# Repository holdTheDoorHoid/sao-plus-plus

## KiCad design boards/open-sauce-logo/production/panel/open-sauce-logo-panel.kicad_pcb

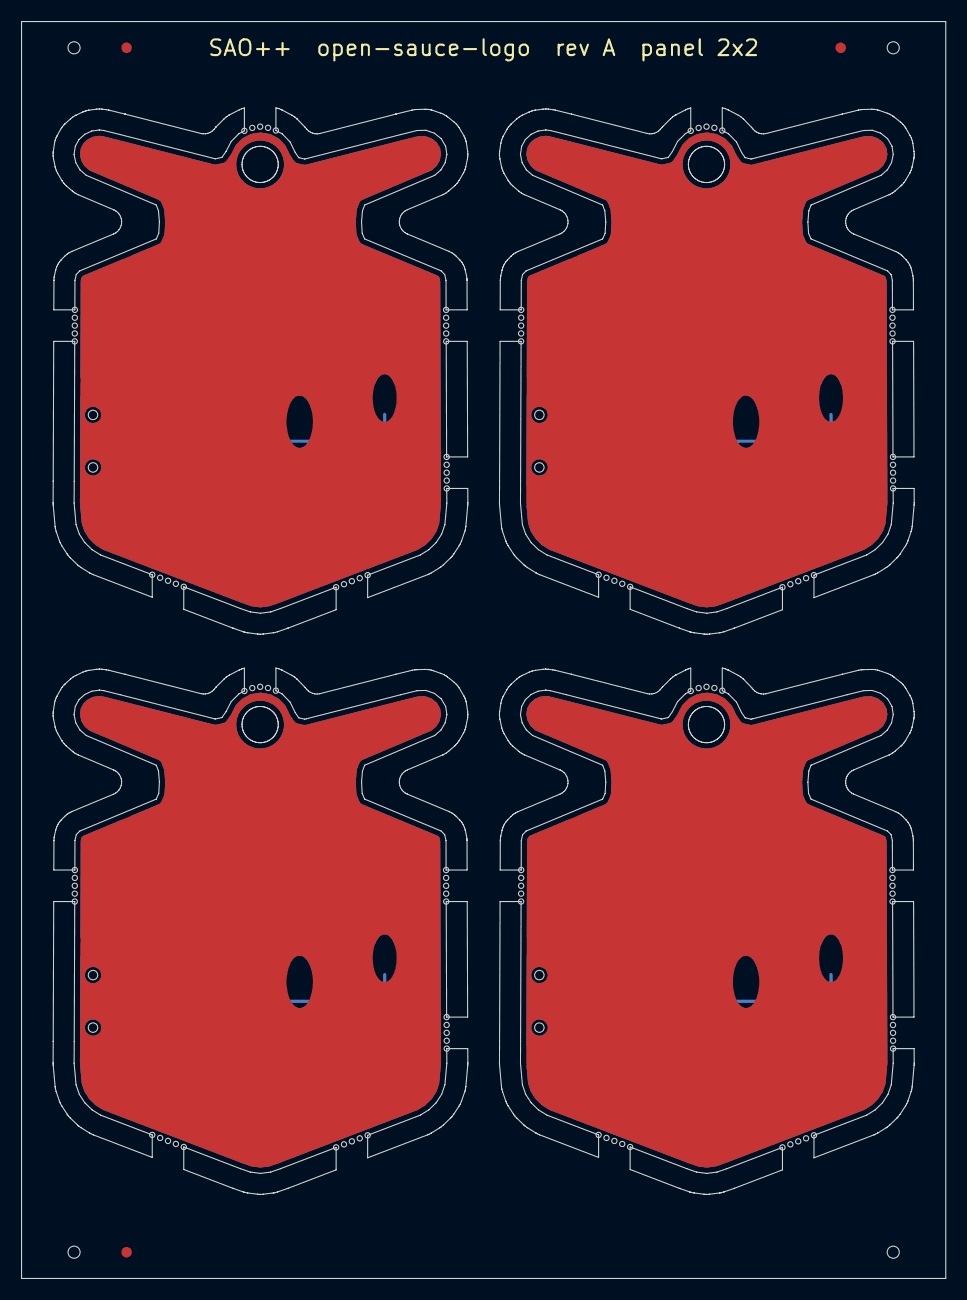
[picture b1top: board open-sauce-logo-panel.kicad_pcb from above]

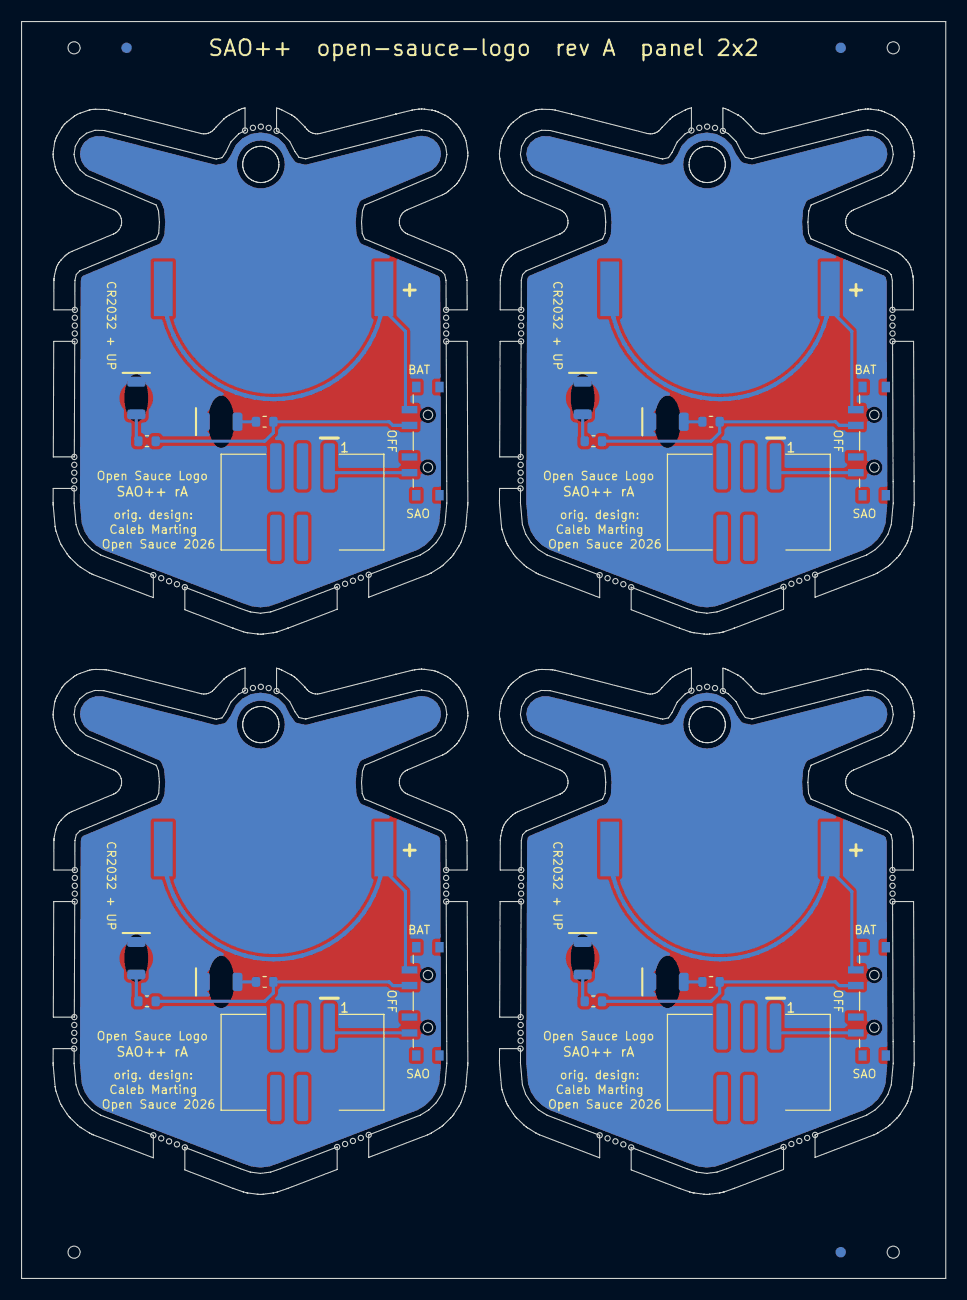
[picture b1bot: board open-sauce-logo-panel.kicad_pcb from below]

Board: 2 copper layers, 88.0 x 119.6 mm, 28 parts (28 on the bottom side), 24 nets.

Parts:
BT101, BT201, BT301, BT401: CR2032; SAOPP_BAT-01_CR2032_SMD_TE_BAT-HLD-001
D101, D102, D201, D202, D301, D302, D401, D402: red; SAOPP_LED-10_1206_ReverseMount_ThroughBoard
J101, J201, J301, J401: SAO v1.69bis; SAOPP_CONN-01_BoxHeader_2x03_P2.54mm_SMD_XFCN_BH254VS-6P
R101, R102, R201, R202, R301, R302, R401, R402: 1.3k; SAOPP_R_0603_1608Metric
SW101, SW201, SW301, SW401: SAO / OFF / BAT; SAOPP_SW-01_Slide_SP3T_CK_PCM13SMTR

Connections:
B2-GND: BT201.2, D201.1, D202.1, J201.2
B2-LED1_A: D201.2, R201.2
B2-LED2_A: D202.2, R202.2
B2-VBAT: BT201.1, SW201.4
B2-VLOAD: R201.1, R202.1, SW201.3
B2-VSAO: J201.1, SW201.1
B3-GND: BT301.2, D301.1, D302.1, J301.2
B3-LED1_A: D301.2, R301.2
B3-LED2_A: D302.2, R302.2
B3-VBAT: BT301.1, SW301.4
B3-VLOAD: R301.1, R302.1, SW301.3
B3-VSAO: J301.1, SW301.1
B4-GND: BT401.2, D401.1, D402.1, J401.2
B4-LED1_A: D401.2, R401.2
B4-LED2_A: D402.2, R402.2
B4-VBAT: BT401.1, SW401.4
B4-VLOAD: R401.1, R402.1, SW401.3
B4-VSAO: J401.1, SW401.1
GND: BT101.2, D101.1, D102.1, J101.2
LED1_A: D101.2, R101.2
LED2_A: D102.2, R102.2
VBAT: BT101.1, SW101.4
VLOAD: R101.1, R102.1, SW101.3
VSAO: J101.1, SW101.1

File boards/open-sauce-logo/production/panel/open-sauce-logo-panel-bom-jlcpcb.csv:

Comment,Designator,Footprint,LCSC Part #
CR2032,"BT101,BT201,BT301,BT401",SAOPP_BAT-01_CR2032_SMD_TE_BAT-HLD-001,C7501066
red,"D101,D102,D201,D202,D301,D302,D401,D402",SAOPP_LED-10_1206_ReverseMount_ThroughBoard,C125107
SAO v1.69bis,"J101,J201,J301,J401",SAOPP_CONN-01_BoxHeader_2x03_P2.54mm_SMD_XFCN_BH254VS-6P,C492445
1.3k,"R101,R102,R201,R202,R301,R302,R401,R402",SAOPP_R_0603_1608Metric,C22767
SAO / OFF / BAT,"SW101,SW201,SW301,SW401",SAOPP_SW-01_Slide_SP3T_CK_PCM13SMTR,C221842

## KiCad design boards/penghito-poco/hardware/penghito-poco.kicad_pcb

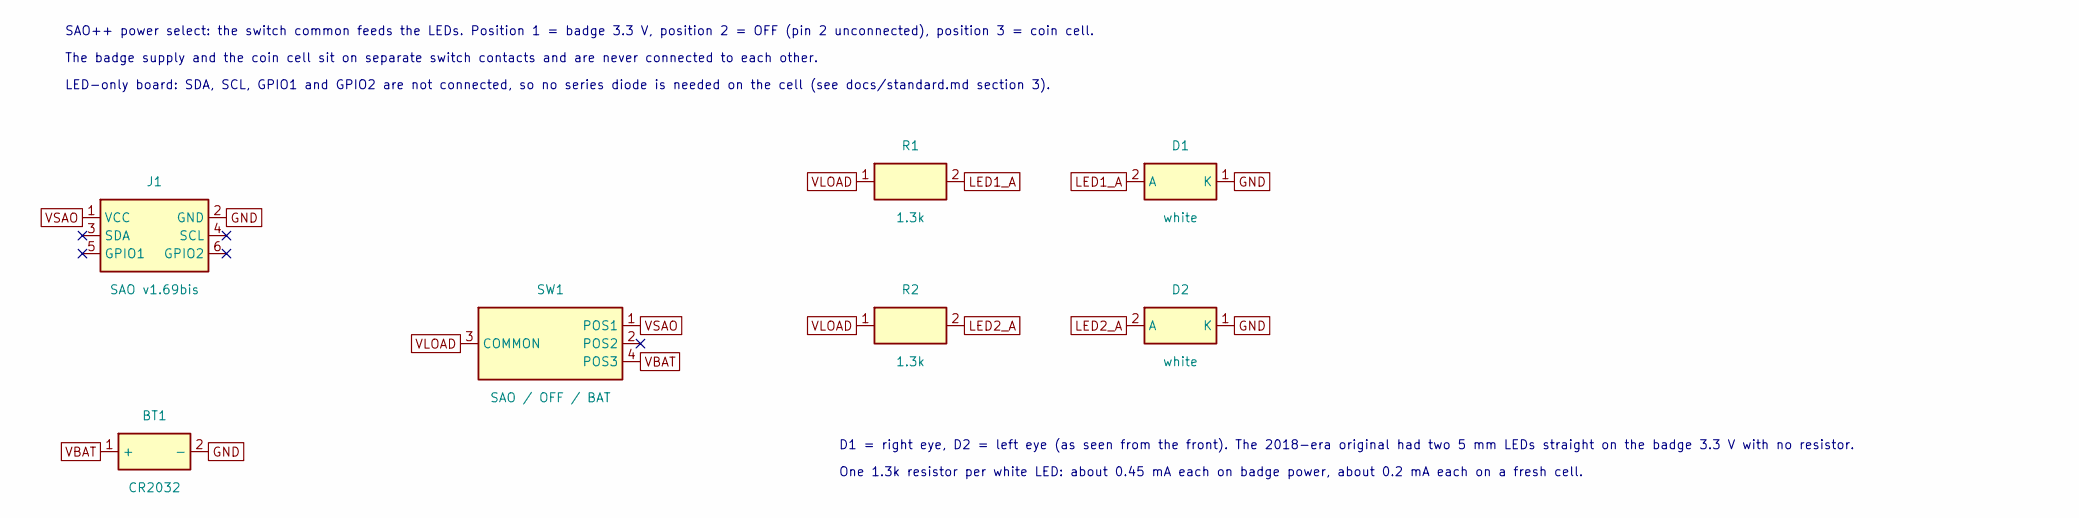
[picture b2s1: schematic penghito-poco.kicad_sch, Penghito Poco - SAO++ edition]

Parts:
BT1: CR2032; SAOPP_BAT-01_CR2032_SMD_TE_BAT-HLD-001; MPN BAT-HLD-001; LCSC C7501066
D1, D2: white; SAOPP_LED-10_1206_ReverseMount_ThroughBoard; MPN LTW-C230DS; LCSC C575513
J1: SAO v1.69bis; SAOPP_CONN-01_BoxHeader_2x03_P2.54mm_SMD_XFCN_BH254VS-6P; MPN BH254VS-6P; LCSC C492445
R1, R2: 1.3k; SAOPP_R_0603_1608Metric; MPN 0603WAF1301T5E; LCSC C22767
SW1: SAO / OFF / BAT; SAOPP_SW-01_Slide_SP3T_CK_PCM13SMTR; MPN PCM13SMTR; LCSC C221842

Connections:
GND: BT1.2 (-), D1.1 (K), D2.1 (K), J1.2 (GND)
LED1_A: D1.2 (A), R1.2
LED2_A: D2.2 (A), R2.2
VBAT: BT1.1 (+), SW1.4 (POS3)
VLOAD: R1.1, R2.1, SW1.3 (COMMON)
VSAO: J1.1 (VCC), SW1.1 (POS1)

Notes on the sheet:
SAO++ power select: the switch common feeds the LEDs. Position 1 = badge 3.3 V, position 2 = OFF (pin 2 unconnected), position 3 = coin cell.
The badge supply and the coin cell sit on separate switch contacts and are never connected to each other.
LED-only board: SDA, SCL, GPIO1 and GPIO2 are not connected, so no series diode is needed on the cell (see docs/standard.md section 3).
D1 = right eye, D2 = left eye (as seen from the front). The 2018-era original had two 5 mm LEDs straight on the badge 3.3 V with no resistor.
One 1.3k resistor per white LED: about 0.45 mA each on badge power, about 0.2 mA each on a fresh cell.

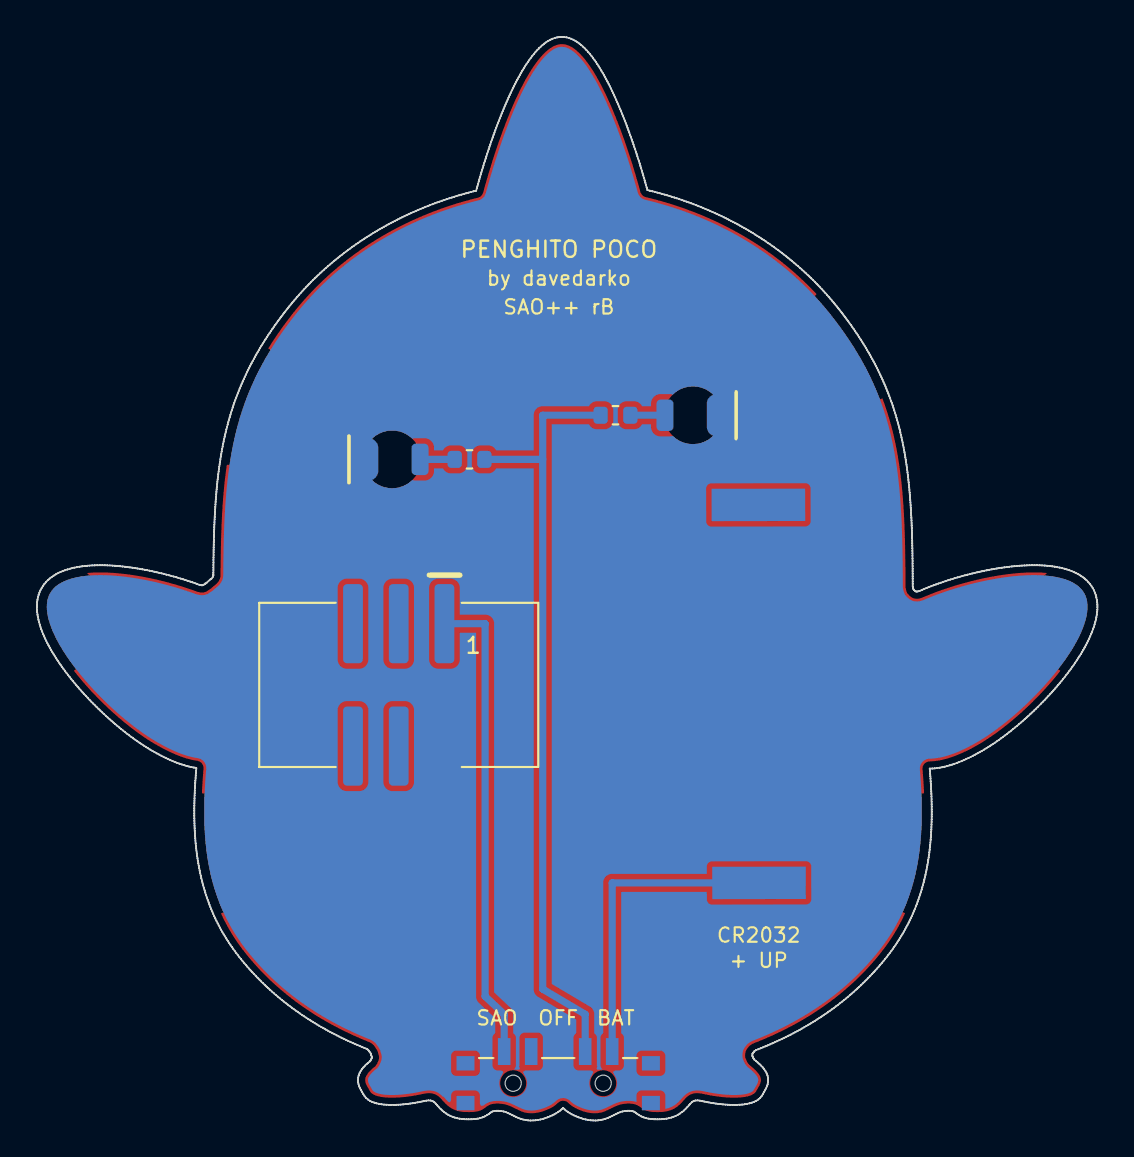
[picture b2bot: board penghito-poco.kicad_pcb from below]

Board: 2 copper layers, 58.9 x 60.2 mm, 7 parts (7 on the bottom side), 6 nets.

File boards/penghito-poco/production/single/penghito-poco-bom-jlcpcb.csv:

Comment,Designator,Footprint,LCSC Part #
CR2032,BT1,SAOPP_BAT-01_CR2032_SMD_TE_BAT-HLD-001,C7501066
white,"D1,D2",SAOPP_LED-10_1206_ReverseMount_ThroughBoard,C575513
SAO v1.69bis,J1,SAOPP_CONN-01_BoxHeader_2x03_P2.54mm_SMD_XFCN_BH254VS-6P,C492445
1.3k,"R1,R2",SAOPP_R_0603_1608Metric,C22767
SAO / OFF / BAT,SW1,SAOPP_SW-01_Slide_SP3T_CK_PCM13SMTR,C221842

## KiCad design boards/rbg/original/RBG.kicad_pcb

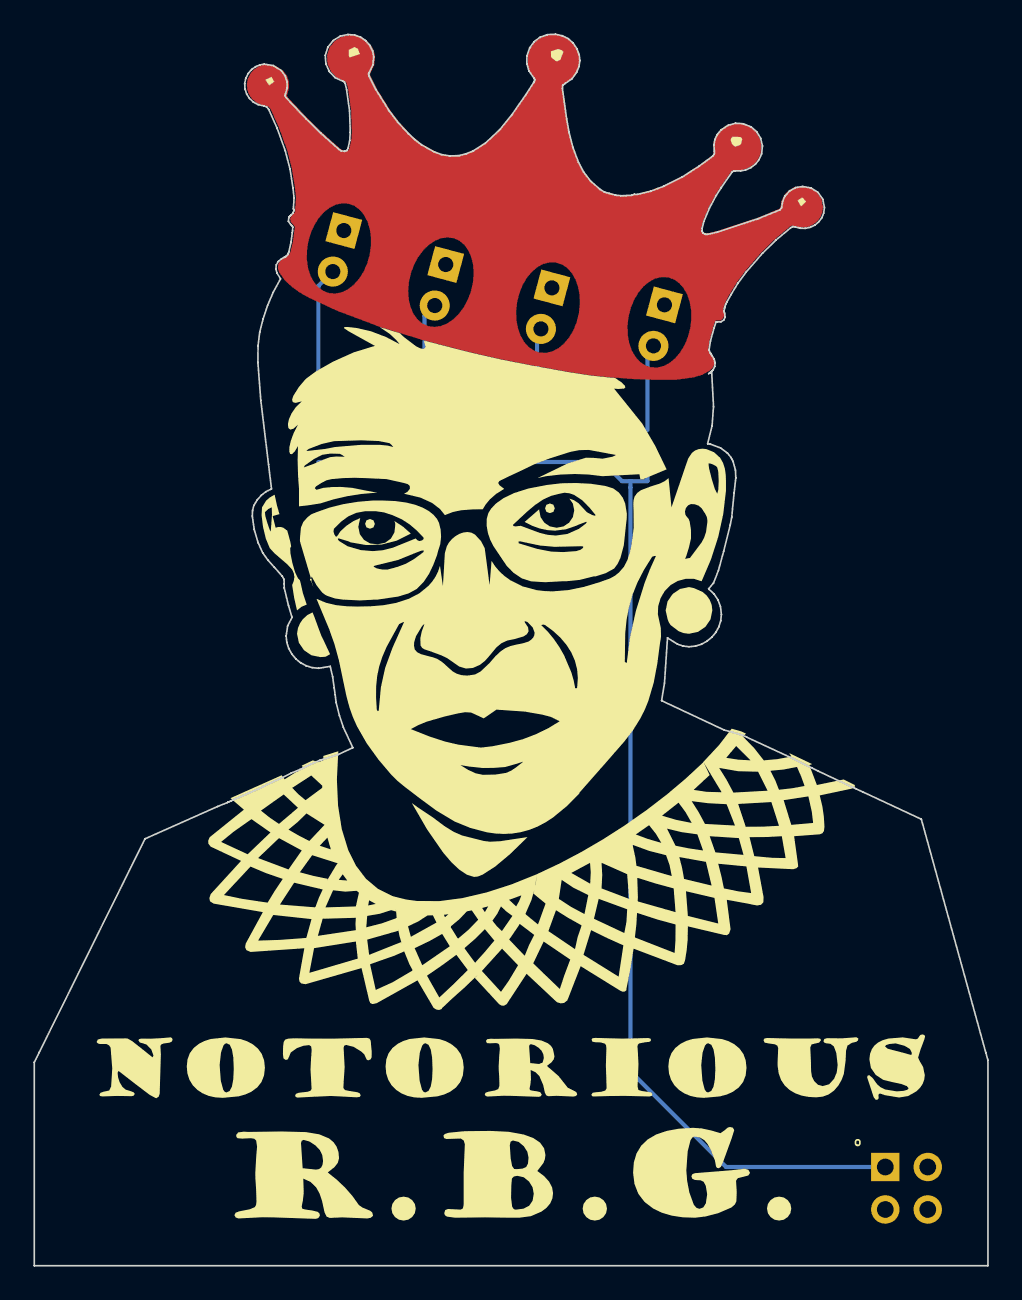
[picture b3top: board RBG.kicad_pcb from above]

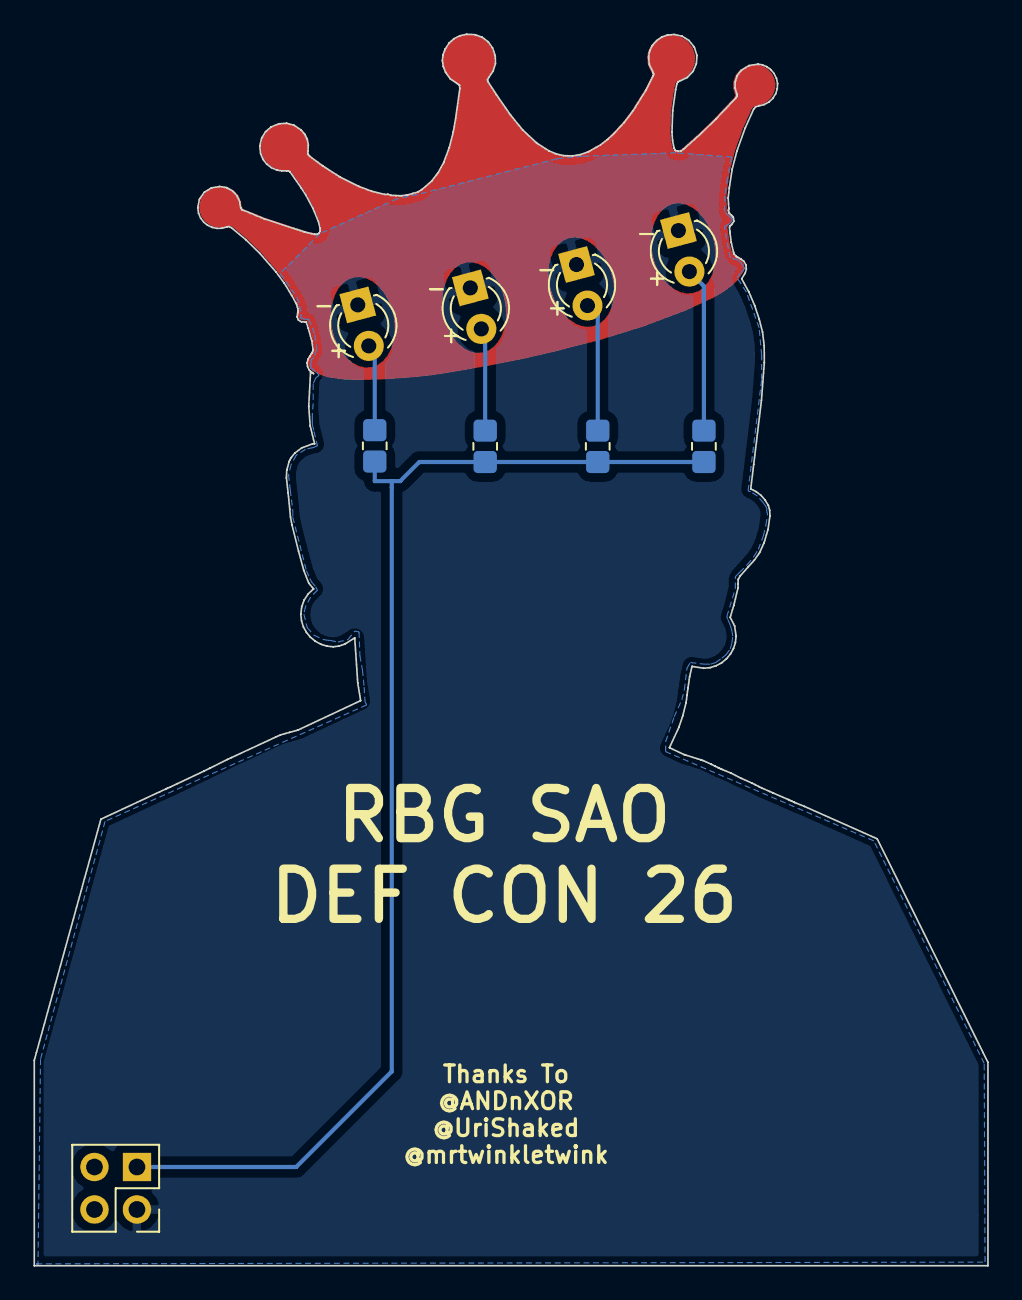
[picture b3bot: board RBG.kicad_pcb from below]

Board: 2 copper layers, 57.0 x 73.7 mm, 10 parts (9 on the bottom side), 6 nets.

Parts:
D1, D2, D3, D4: LED; LED_D3.0mm_FlatTop
J1: Conn_02x02_Odd_Even; PinHeader_2x02_P2.54mm_Vertical_edit
R1, R2, R3, R4: R; R_0805_2012Metric_Pad1.33x1.40mm_HandSolder
svg2mod: G***; rbg

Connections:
unnamed: D1.1, D2.1, D3.1, D4.1, J1.3
unnamed: D1.2, R1.1
unnamed: D2.2, R2.1
unnamed: D3.2, R3.1
unnamed: D4.2, R4.1
unnamed: J1.1, R1.2, R2.2, R3.2, R4.2

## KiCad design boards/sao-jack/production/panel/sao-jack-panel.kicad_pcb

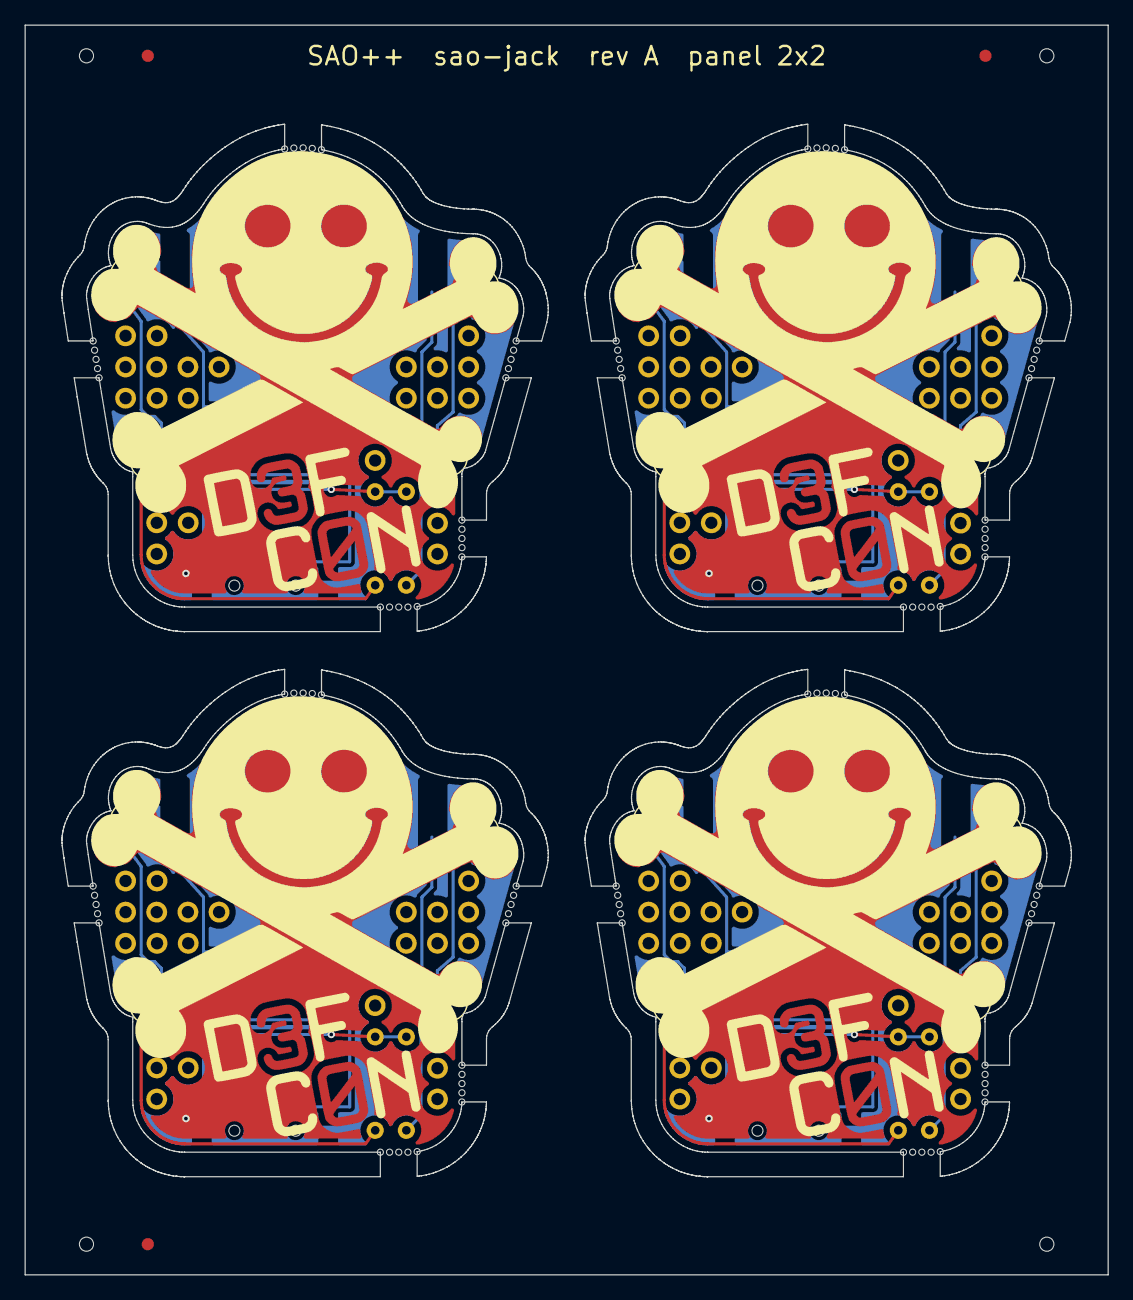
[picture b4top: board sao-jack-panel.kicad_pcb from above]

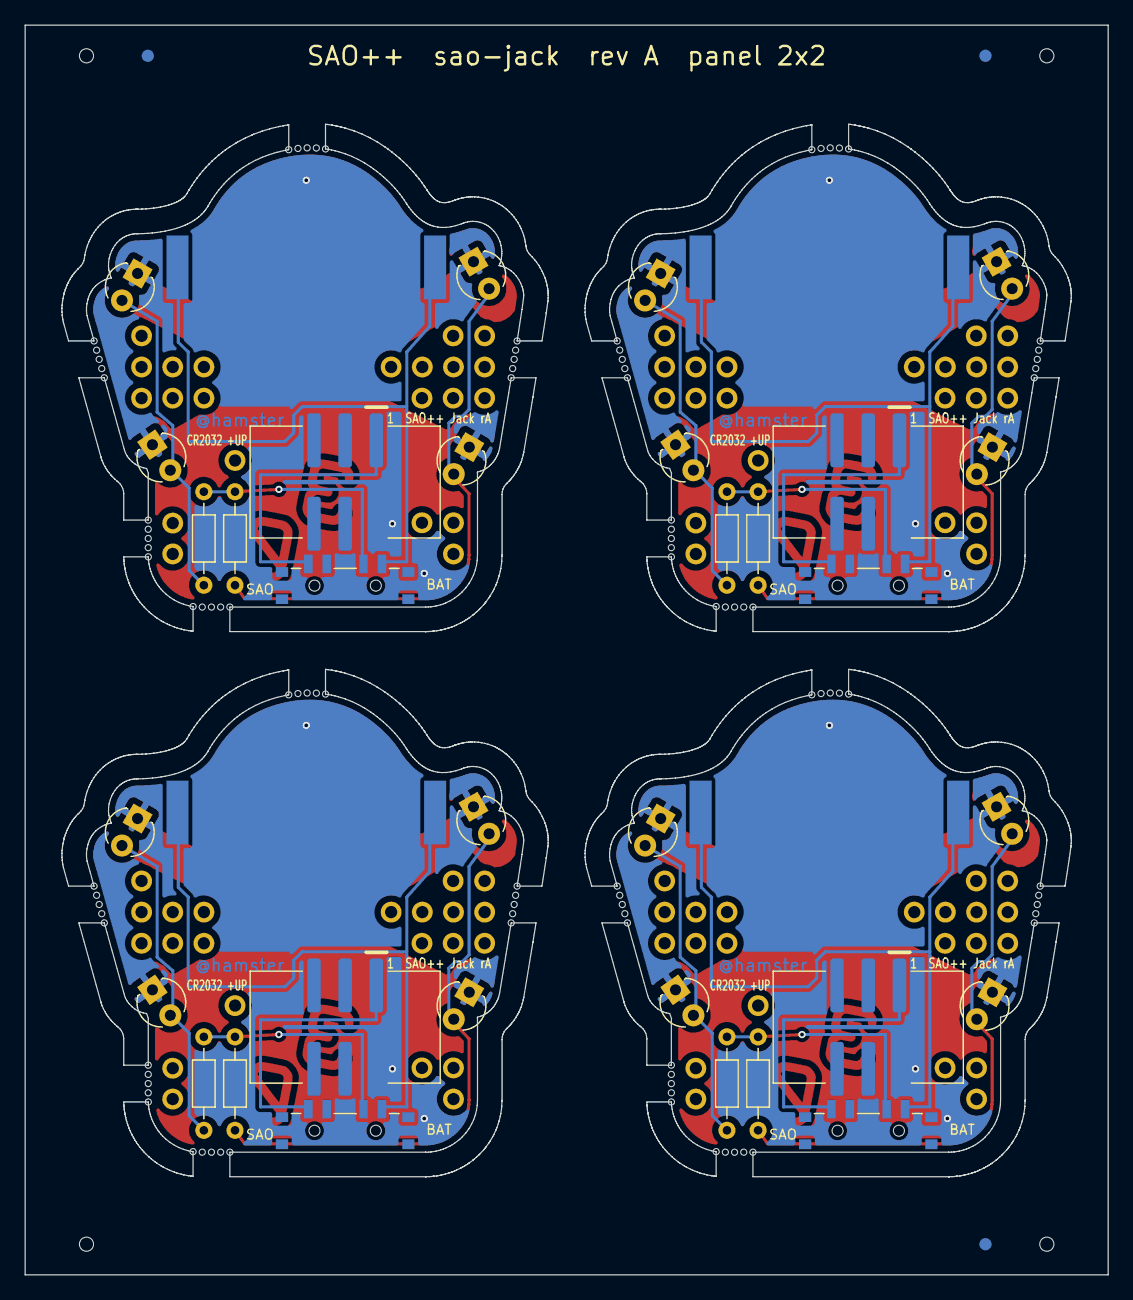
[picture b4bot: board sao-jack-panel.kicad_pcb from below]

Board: 2 copper layers, 88.3 x 101.9 mm, 36 parts (20 on the bottom side), 24 nets.

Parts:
BT101, BT201, BT301, BT401: CR2032; SAOPP_BAT-01_CR2032_SMD_TE_BAT-HLD-001
D101, D103, D201, D203, D301, D303, D401, D403: LED 3 mm (maker: green); LED_D3.0mm
D102, D104, D202, D204, D302, D304, D402, D404: LED 3 mm (maker: red); LED_D3.0mm
J101, J201, J301, J401: SAO v1.69bis; SAOPP_CONN-01_BoxHeader_2x03_P2.54mm_SMD_XFCN_BH254VS-6P
R101, R102, R201, R202, R301, R302, R401, R402: 680; R_Axial_DIN0204_L3.6mm_D1.6mm_P7.62mm_Horizontal
SW101, SW201, SW301, SW401: SAO / OFF / BAT; SAOPP_SW-01_Slide_SP3T_CK_PCM13SMTR

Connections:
B2-GND: BT201.2, D201.1, D202.1, D203.1, D204.1, J201.2
B2-LED_L: D201.2, D203.2, R201.1
B2-LED_R: D202.2, D204.2, R202.1
B2-VBAT: BT201.1, SW201.4
B2-VLOAD: R201.2, R202.2, SW201.3
B2-VSAO: J201.1, SW201.1
B3-GND: BT301.2, D301.1, D302.1, D303.1, D304.1, J301.2
B3-LED_L: D301.2, D303.2, R301.1
B3-LED_R: D302.2, D304.2, R302.1
B3-VBAT: BT301.1, SW301.4
B3-VLOAD: R301.2, R302.2, SW301.3
B3-VSAO: J301.1, SW301.1
B4-GND: BT401.2, D401.1, D402.1, D403.1, D404.1, J401.2
B4-LED_L: D401.2, D403.2, R401.1
B4-LED_R: D402.2, D404.2, R402.1
B4-VBAT: BT401.1, SW401.4
B4-VLOAD: R401.2, R402.2, SW401.3
B4-VSAO: J401.1, SW401.1
GND: BT101.2, D101.1, D102.1, D103.1, D104.1, J101.2
LED_L: D101.2, D103.2, R101.1
LED_R: D102.2, D104.2, R102.1
VBAT: BT101.1, SW101.4
VLOAD: R101.2, R102.2, SW101.3
VSAO: J101.1, SW101.1

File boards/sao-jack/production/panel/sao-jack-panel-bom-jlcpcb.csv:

Comment,Designator,Footprint,LCSC Part #
CR2032,"BT101,BT201,BT301,BT401",SAOPP_BAT-01_CR2032_SMD_TE_BAT-HLD-001,C7501066
SAO v1.69bis,"J101,J201,J301,J401",SAOPP_CONN-01_BoxHeader_2x03_P2.54mm_SMD_XFCN_BH254VS-6P,C492445
SAO / OFF / BAT,"SW101,SW201,SW301,SW401",SAOPP_SW-01_Slide_SP3T_CK_PCM13SMTR,C221842

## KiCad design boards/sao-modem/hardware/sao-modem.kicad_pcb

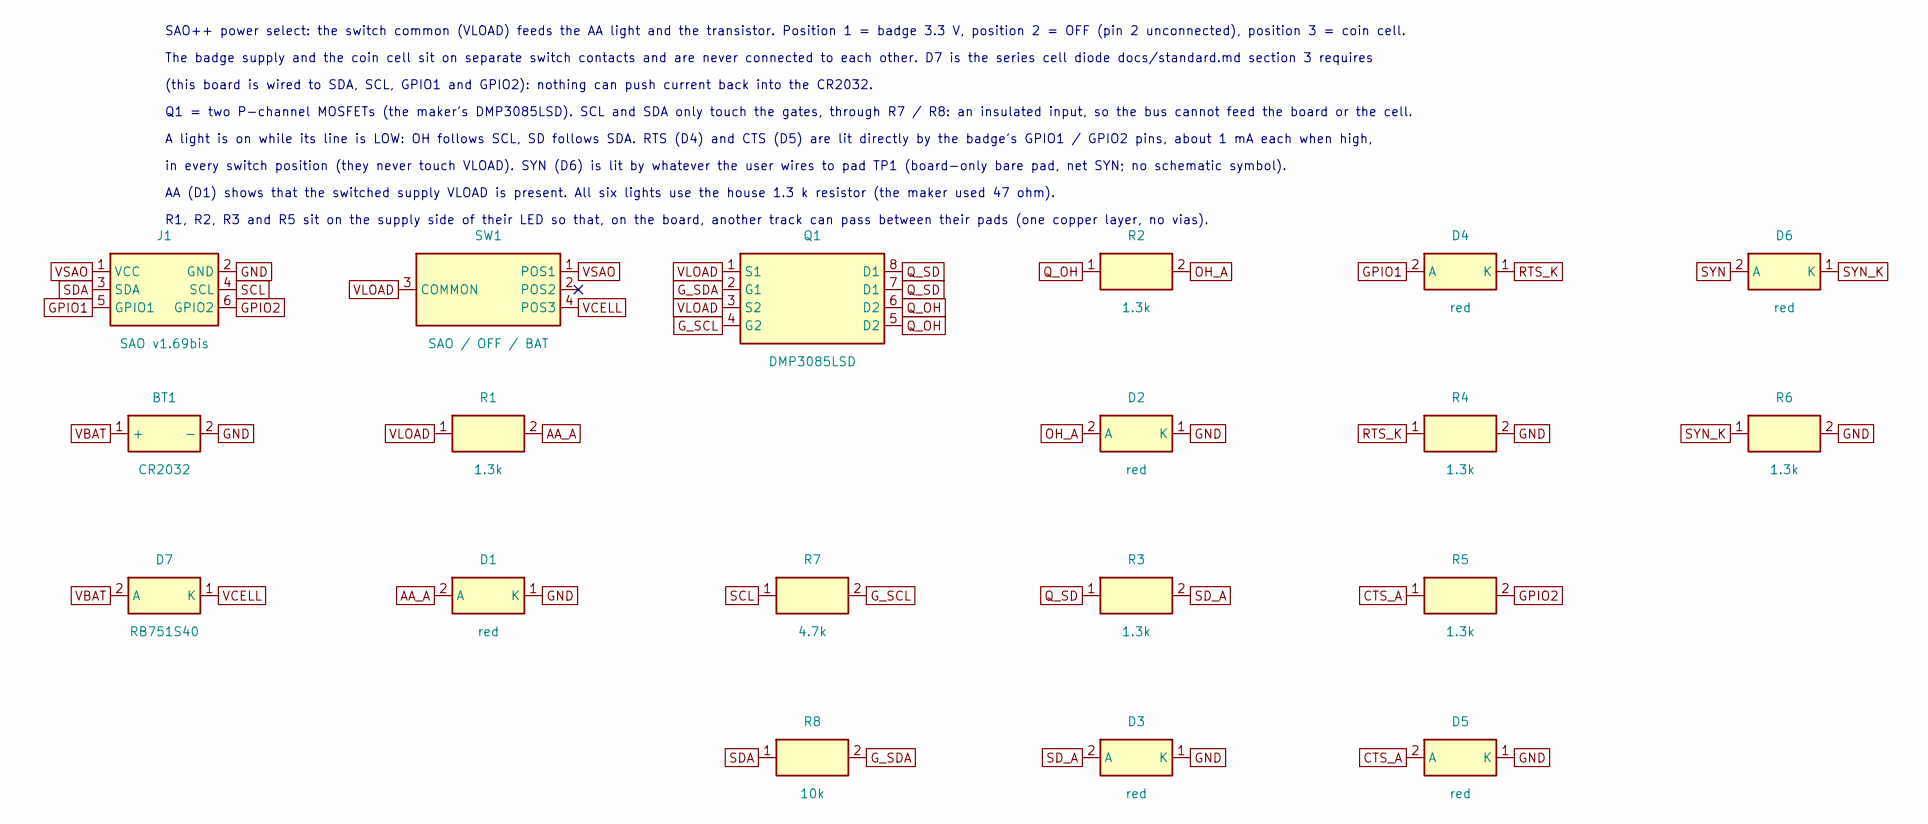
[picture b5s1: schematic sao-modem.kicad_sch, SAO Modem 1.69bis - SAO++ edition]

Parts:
BT1: CR2032; SAOPP_BAT-01_CR2032_SMD_TE_BAT-HLD-001; MPN BAT-HLD-001; LCSC C7501066
D1, D2, D3, D4, D5, D6: red; SAOPP_LED-10_1206_ReverseMount_ThroughBoard; MPN LTST-C230KRKT; LCSC C125107
D7: RB751S40; D_SOD-523; MPN RB751S40T1G; LCSC C232576
J1: SAO v1.69bis; SAOPP_CONN-01_BoxHeader_2x03_P2.54mm_SMD_XFCN_BH254VS-6P; MPN BH254VS-6P; LCSC C492445
Q1: DMP3085LSD; SOIC-8_3.9x4.9mm_P1.27mm; MPN DMP3085LSD-13
R1, R2, R3, R4, R5, R6: 1.3k; SAOPP_R_0603_1608Metric; MPN 0603WAF1301T5E; LCSC C22767
R7: 4.7k; R_0603_1608Metric; MPN RMCF0603JT4K70
R8: 10k; R_0603_1608Metric; MPN RMCF0603JT10K0
SW1: SAO / OFF / BAT; SAOPP_SW-01_Slide_SP3T_CK_PCM13SMTR; MPN PCM13SMTR; LCSC C221842

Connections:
AA_A: D1.2 (A), R1.2
CTS_A: D5.2 (A), R5.1
GND: BT1.2 (-), D1.1 (K), D2.1 (K), D3.1 (K), D5.1 (K), J1.2 (GND), R4.2, R6.2
GPIO1: D4.2 (A), J1.5 (GPIO1)
GPIO2: J1.6 (GPIO2), R5.2
G_SCL: Q1.4 (G2), R7.2
G_SDA: Q1.2 (G1), R8.2
OH_A: D2.2 (A), R2.2
Q_OH: Q1.5 (D2), Q1.6 (D2), R2.1
Q_SD: Q1.7 (D1), Q1.8 (D1), R3.1
RTS_K: D4.1 (K), R4.1
SCL: J1.4 (SCL), R7.1
SDA: J1.3 (SDA), R8.1
SD_A: D3.2 (A), R3.2
SYN: D6.2 (A); also elsewhere on the board
SYN_K: D6.1 (K), R6.1
VBAT: BT1.1 (+), D7.2 (A)
VCELL: D7.1 (K), SW1.4 (POS3)
VLOAD: Q1.1 (S1), Q1.3 (S2), R1.1, SW1.3 (COMMON)
VSAO: J1.1 (VCC), SW1.1 (POS1)

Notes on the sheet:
SAO++ power select: the switch common (VLOAD) feeds the AA light and the transistor. Position 1 = badge 3.3 V, position 2 = OFF (pin 2 unconnected), position 3 = coin cell.
The badge supply and the coin cell sit on separate switch contacts and are never connected to each other. D7 is the series cell diode docs/standard.md section 3 requires
(this board is wired to SDA, SCL, GPIO1 and GPIO2): nothing can push current back into the CR2032.
Q1 = two P-channel MOSFETs (the maker's DMP3085LSD). SCL and SDA only touch the gates, through R7 / R8: an insulated input, so the bus cannot feed the board or the cell.
A light is on while its line is LOW: OH follows SCL, SD follows SDA. RTS (D4) and CTS (D5) are lit directly by the badge's GPIO1 / GPIO2 pins, about 1 mA each when high,
in every switch position (they never touch VLOAD). SYN (D6) is lit by whatever the user wires to pad TP1 (board-only bare pad, net SYN; no schematic symbol).
AA (D1) shows that the switched supply VLOAD is present. All six lights use the house 1.3 k resistor (the maker used 47 ohm).
R1, R2, R3 and R5 sit on the supply side of their LED so that, on the board, another track can pass between their pads (one copper layer, no vias).

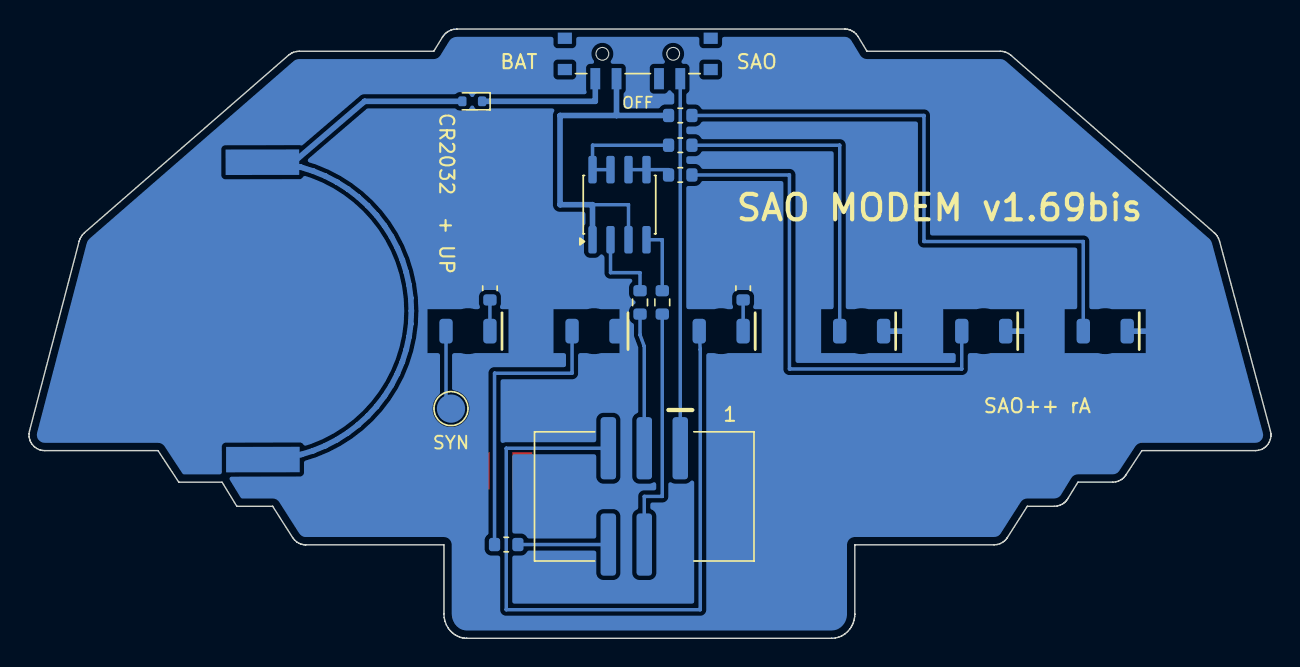
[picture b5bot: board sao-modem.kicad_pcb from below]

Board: 2 copper layers, 87.7 x 43.0 mm, 20 parts (20 on the bottom side), 20 nets.

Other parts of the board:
TP1: SYN pad; TestPoint_Pad_D2.0mm

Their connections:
SYN: TP1.1; also elsewhere on the board

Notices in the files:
boards/sao-jack/production/panel/sao-jack-panel.kicad_pcb:
Original design: hamster, DEF CON 30 SAO Jack 1.0 (2022), MIT license, github.com/hamster/defcon30
boards/sao-modem/hardware/sao-modem.kicad_pcb:
Original design: hamster (@hamster), SAO Modem 1.69bis, DEF CON 30, MIT license, github.com/hamster/defcon30
